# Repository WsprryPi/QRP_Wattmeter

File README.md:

# QRP RF Wattmeter: *A compact RF power meter designed for QRP transmitters.*

This project provides hardware and firmware for measuring RF output power and displaying the result digitally. The hardware is designed as a **carrier board (shield-style daughterboard)** that accepts an ESP32 module as a plug‑in controller.

The current reference controller board is the **Heltec WiFi LoRa 32 V3**, although this project does **not use WiFi, Bluetooth, or LoRa**.  
The module is used strictly as a convenient ESP32 microcontroller platform with integrated USB power and programming support.

---

## Project Overview

This repository contains a complete RF wattmeter system for low‑power transmitters.

The system consists of:

- RF sampling network
- RF power detector stage
- Analog conditioning amplifier
- ESP32 microcontroller interface
- Digital power display

The measurement front end converts RF power into a DC voltage that is read by the ESP32 ADC.  
Firmware then converts this value into calibrated RF power measurements.

---

## Hardware Architecture

The hardware implements the following signal chain:

RF input → sampling network → RF detector → analog scaling → ESP32 ADC

The detector stage converts RF power to a logarithmic DC voltage.  
An analog amplifier conditions this voltage so that the ESP32 ADC can measure it with good resolution.

The ESP32 then performs:

- ADC sampling
- calibration compensation
- power calculation
- display output

---

## ESP32 Controller Board

This design is intended to use the [Heltec WiFi LoRa 32 V3](https://heltec.org/project/wifi-lora-32-v3/) module as the controller board.

The module plugs into the wattmeter carrier board and provides:

- ESP32 microcontroller
- USB power and programming
- GPIO access
- ADC input

For this project:

- WiFi is not used
- Bluetooth is not used
- LoRa is not used

The board simply provides a convenient ESP32 platform.

---

## Hardware Features

- RF sampling tap for transmitter output
- RF power detection stage
- analog filtering and scaling
- ESP32 ADC interface
- calibration support
- test points for measurement and debugging
- plug‑in ESP32 controller module

The design is intended for **QRP transmitters up to approximately 1 W**.

---

## Documentation

Full documentation is available in the `docs/` directory and is designed to build with **Sphinx**.

The documentation covers:

- hardware overview
- schematic explanation
- PCB layout notes
- firmware architecture
- RF design details
- calibration procedure

---

## Calibration

Calibration is performed in software using known RF power levels.

Typical calibration procedure:

1. Connect a known RF source and dummy load
2. Apply known RF power levels
3. Record ADC values
4. Store calibration constants in firmware

The firmware then converts ADC readings into power values.

---

## Intended Use

This project is intended for:

- QRP transmitters
- amateur radio experiments
- RF measurement tools
- embedded firmware projects

---

## License

See the [LICENSE](LICENSE.md) file in this repository.

---

## Contributing

Pull requests, improvements, and suggestions are welcome.

<!-- Future Additions:

	•	schematic preview image
	•	project block diagram
	•	badges (RTD, license, build status)
	•	rendered directory tree
	•	calibration example plots
 -->

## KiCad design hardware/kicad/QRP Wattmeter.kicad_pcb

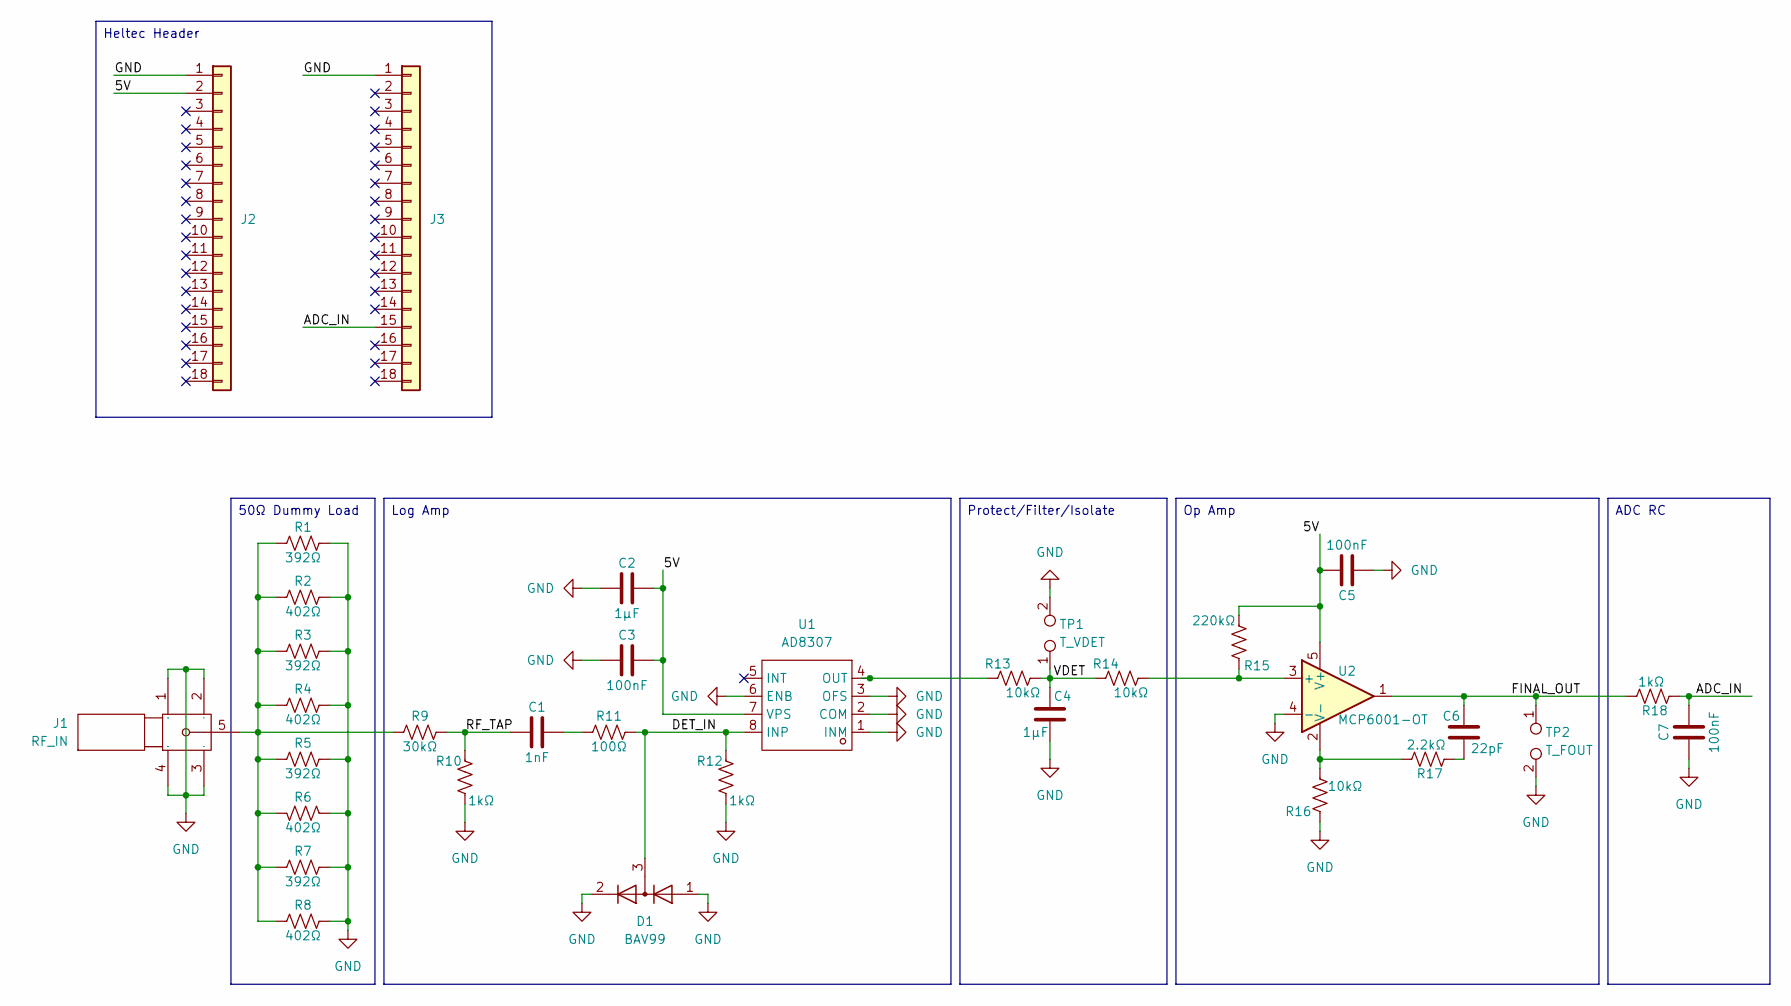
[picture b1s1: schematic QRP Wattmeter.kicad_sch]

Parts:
C1: 1nF; C_0603_1608Metric; LCSC_PART C106246
C2, C4: 1µF; C_0603_1608Metric; LCSC_PART C15849
C3, C5, C7: 100nF; C_0603_1608Metric; LCSC_PART C14663
C6: 22pF; C_0603_1608Metric; LCSC_PART C1653
D1: BAV99; SOT-23; LCSC_PART C2500
J1: RF_IN; SMA-TH_BWSMA-KWE-Z001; Manufacturer Part BWSMA-KWE-Z001; LCSC Part Name 内孔 SMA 弯头
J2, J3: Conn_01x18; PinSocket_1x18_P2.54mm_Vertical; LCSC_PART C2897381
R1, R3, R5, R7: 392Ω; R_1206_3216Metric; LCSC_PART C3013254
R2, R4, R6, R8: 402Ω; R_1206_3216Metric; LCSC_PART C274025
R9: 30kΩ; R_0603_1608Metric; LCSC_PART C22984
R10, R18: 1kΩ; R_0603_1608Metric; LCSC_PART C21190
R11: 100Ω; R_0603_1608Metric; LCSC_PART C25803
R12: 1kΩ; R_0402_1005Metric; LCSC_PART C11702
R13, R14, R16: 10kΩ; R_0603_1608Metric; LCSC_PART C25804
R15: 220kΩ; R_0603_1608Metric; LCSC_PART C22961
R17: 2.2kΩ; R_0603_1608Metric; LCSC_PART C4190
TP1: T_VDET; TestPoint_2Pads_Pitch2.54mm_Drill0.8mm
TP2: T_FOUT; TestPoint_2Pads_Pitch2.54mm_Drill0.8mm
U1: AD8307; SOIC-8_L4.9-W3.9-P1.27-LS6.0-BL; Manufacturer Part AD8307ARZ-REEL; LCSC Part Name 低功耗 DC 至 500 MHz 92 dB 对数放大器
U2: MCP6001-OT; SOT-23-5; LCSC_PART C116490

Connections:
/5V: C2.2, C3.2, C5.2, J2.2, R15.2, U1.7 (VPS), U2.5 (V+)
/ADC_IN: C7.2, J3.15, R18.1
/DET_IN: D1.3 (K), R11.2, R12.2, U1.8 (INP)
/FINAL_OUT: C6.2, R18.2, TP2.1, U2.1
/RF_TAP: C1.1, R9.2, R10.2
/VDET: C4.1, R13.1, R14.2, TP1.1
GND: C2.1, C3.1, C4.2, C5.1, C7.1, D1.1 (K), D1.2 (A), J1.1, J1.2, J1.3, J1.4, J2.1, J3.1, R1.2, R2.2, R3.2, R4.2, R5.2, R6.1, R7.2, R8.2, R10.1, R12.1, R16.2, TP1.2, TP2.2, U1.1 (INM), U1.2 (COM), U1.3 (OFS), U1.6 (ENB), U2.4 (-)
unnamed: C1.2, R11.1
unnamed: C6.1, R17.1
unnamed: J1.5, R1.1, R2.1, R3.1, R4.1, R5.1, R6.2, R7.1, R8.1, R9.1
unnamed: R13.2, U1.4 (OUT)
unnamed: R14.1, R15.1, U2.3 (+)
unnamed: R16.1, R17.2, U2.2 (V-)

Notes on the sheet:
Protect/Filter/Isolate
Log Amp
50Ω Dummy Load
Op Amp
Heltec Header
ADC RC

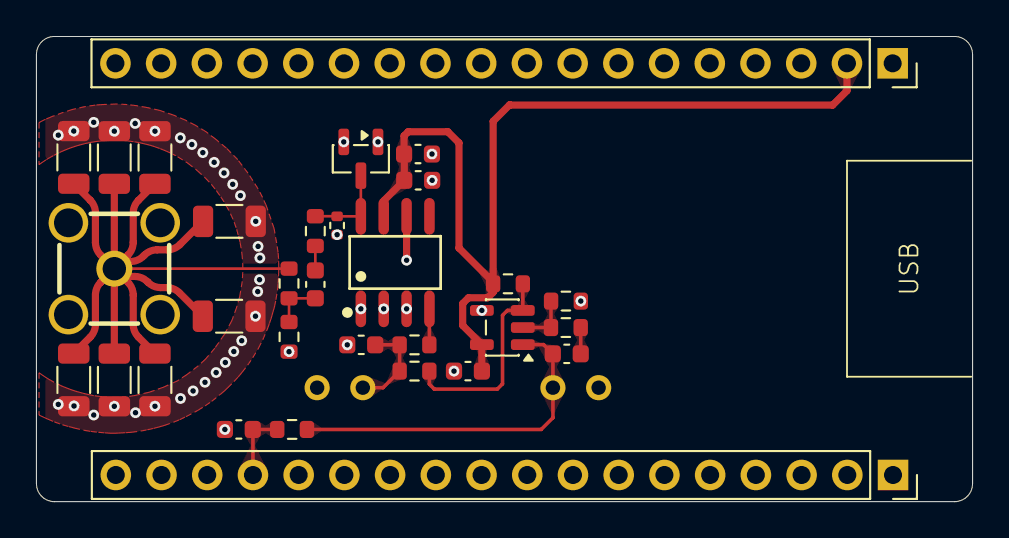
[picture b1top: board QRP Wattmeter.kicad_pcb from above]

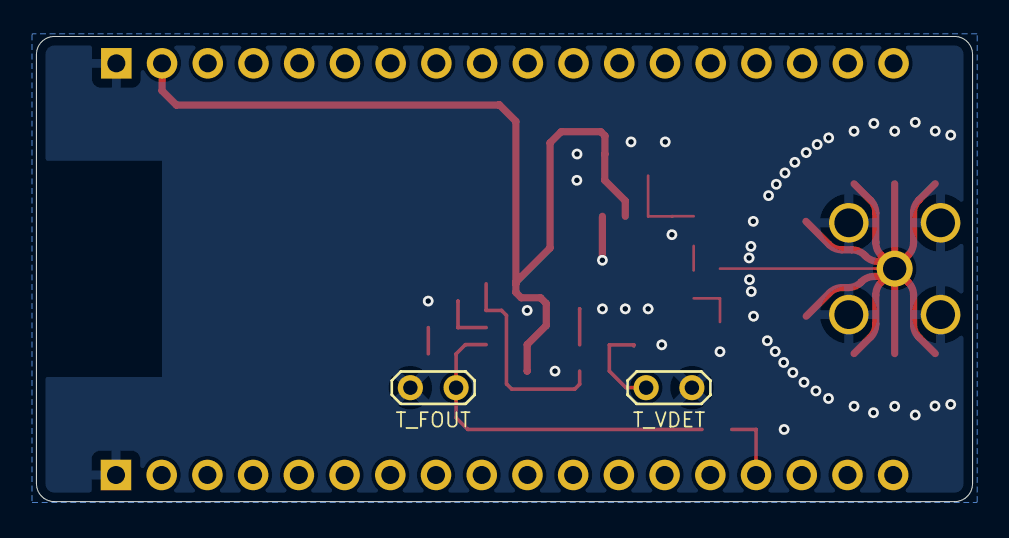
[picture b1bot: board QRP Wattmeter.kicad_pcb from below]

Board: 2 copper layers, 52.0 x 25.8 mm, 33 parts (2 on the bottom side), 13 nets.

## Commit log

2026-03-11 Initial repo commit
